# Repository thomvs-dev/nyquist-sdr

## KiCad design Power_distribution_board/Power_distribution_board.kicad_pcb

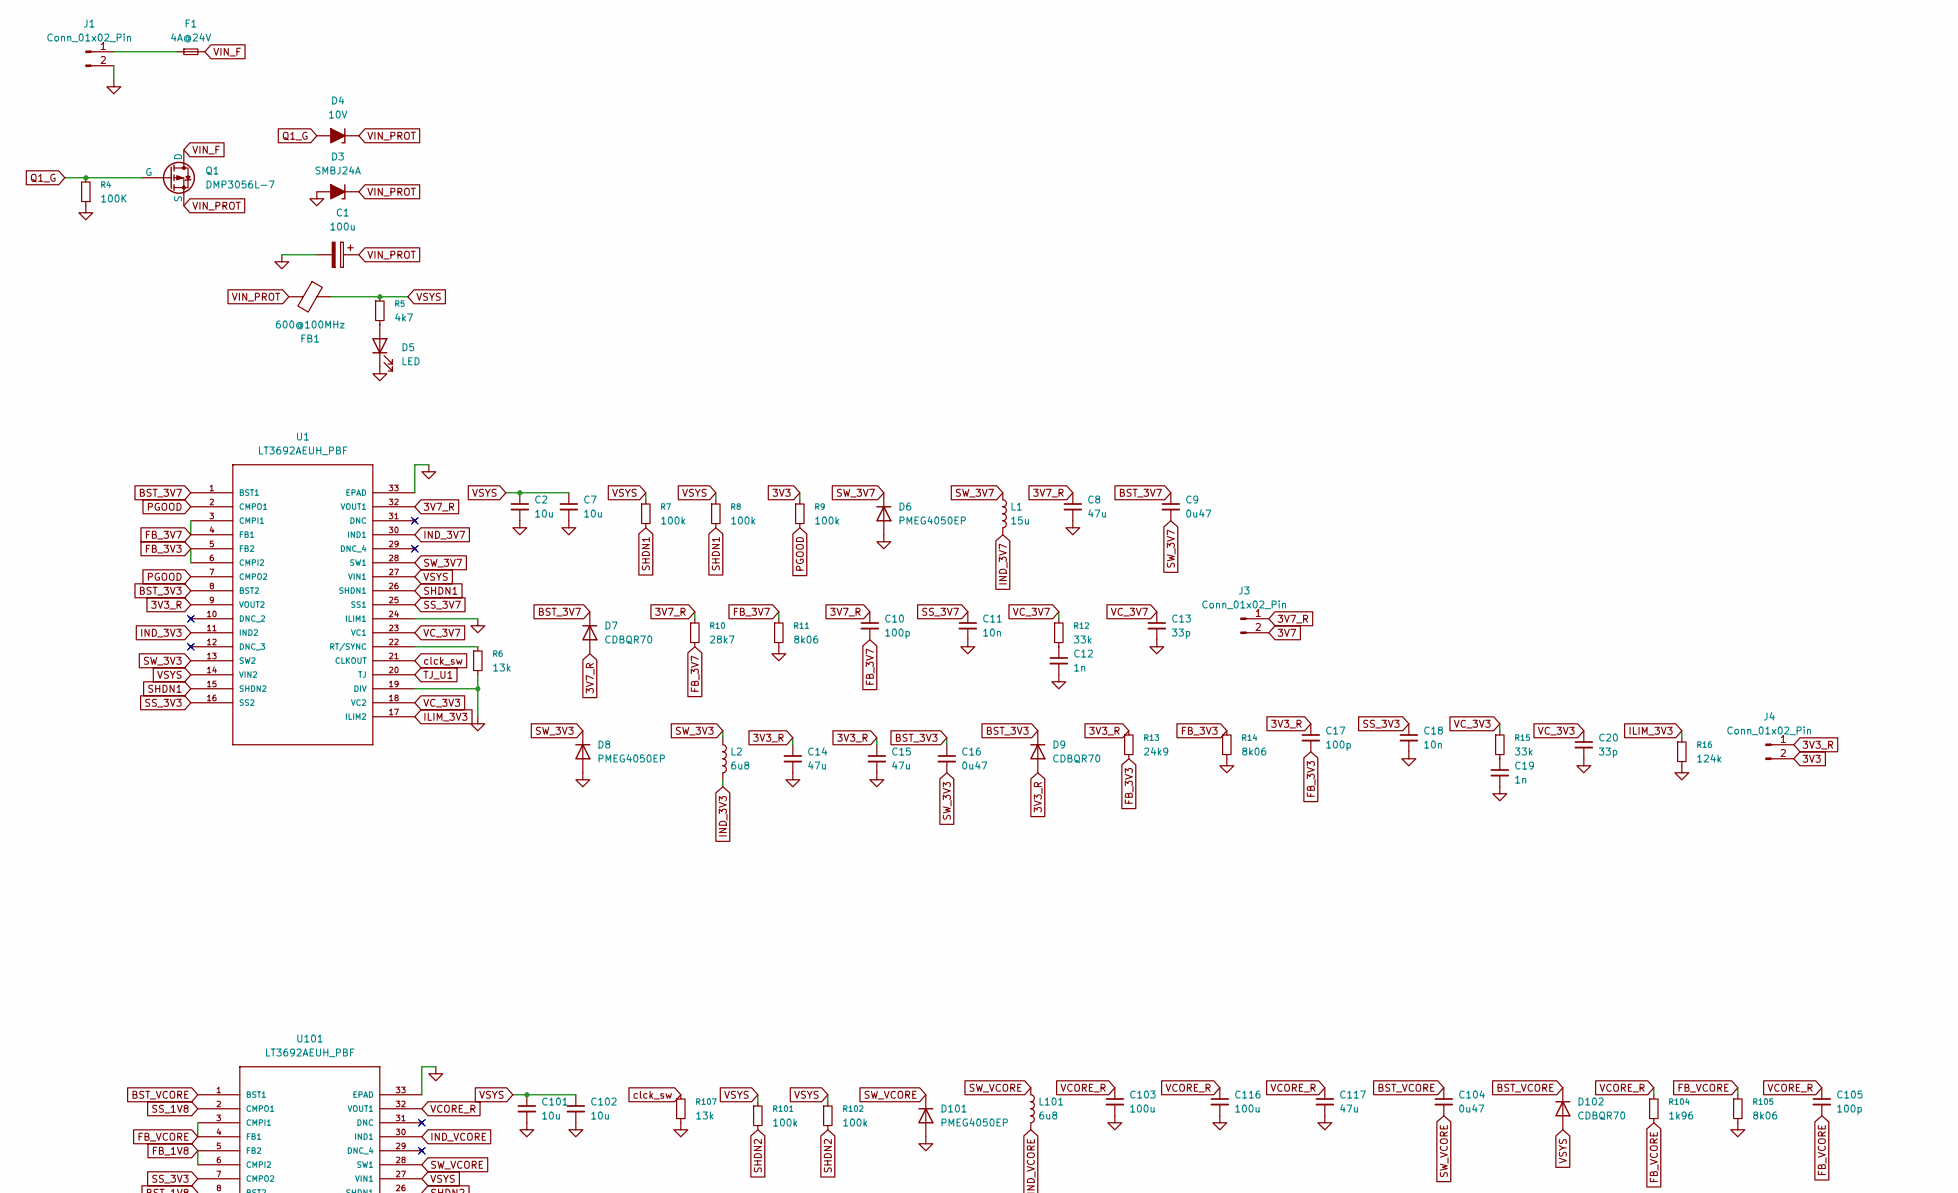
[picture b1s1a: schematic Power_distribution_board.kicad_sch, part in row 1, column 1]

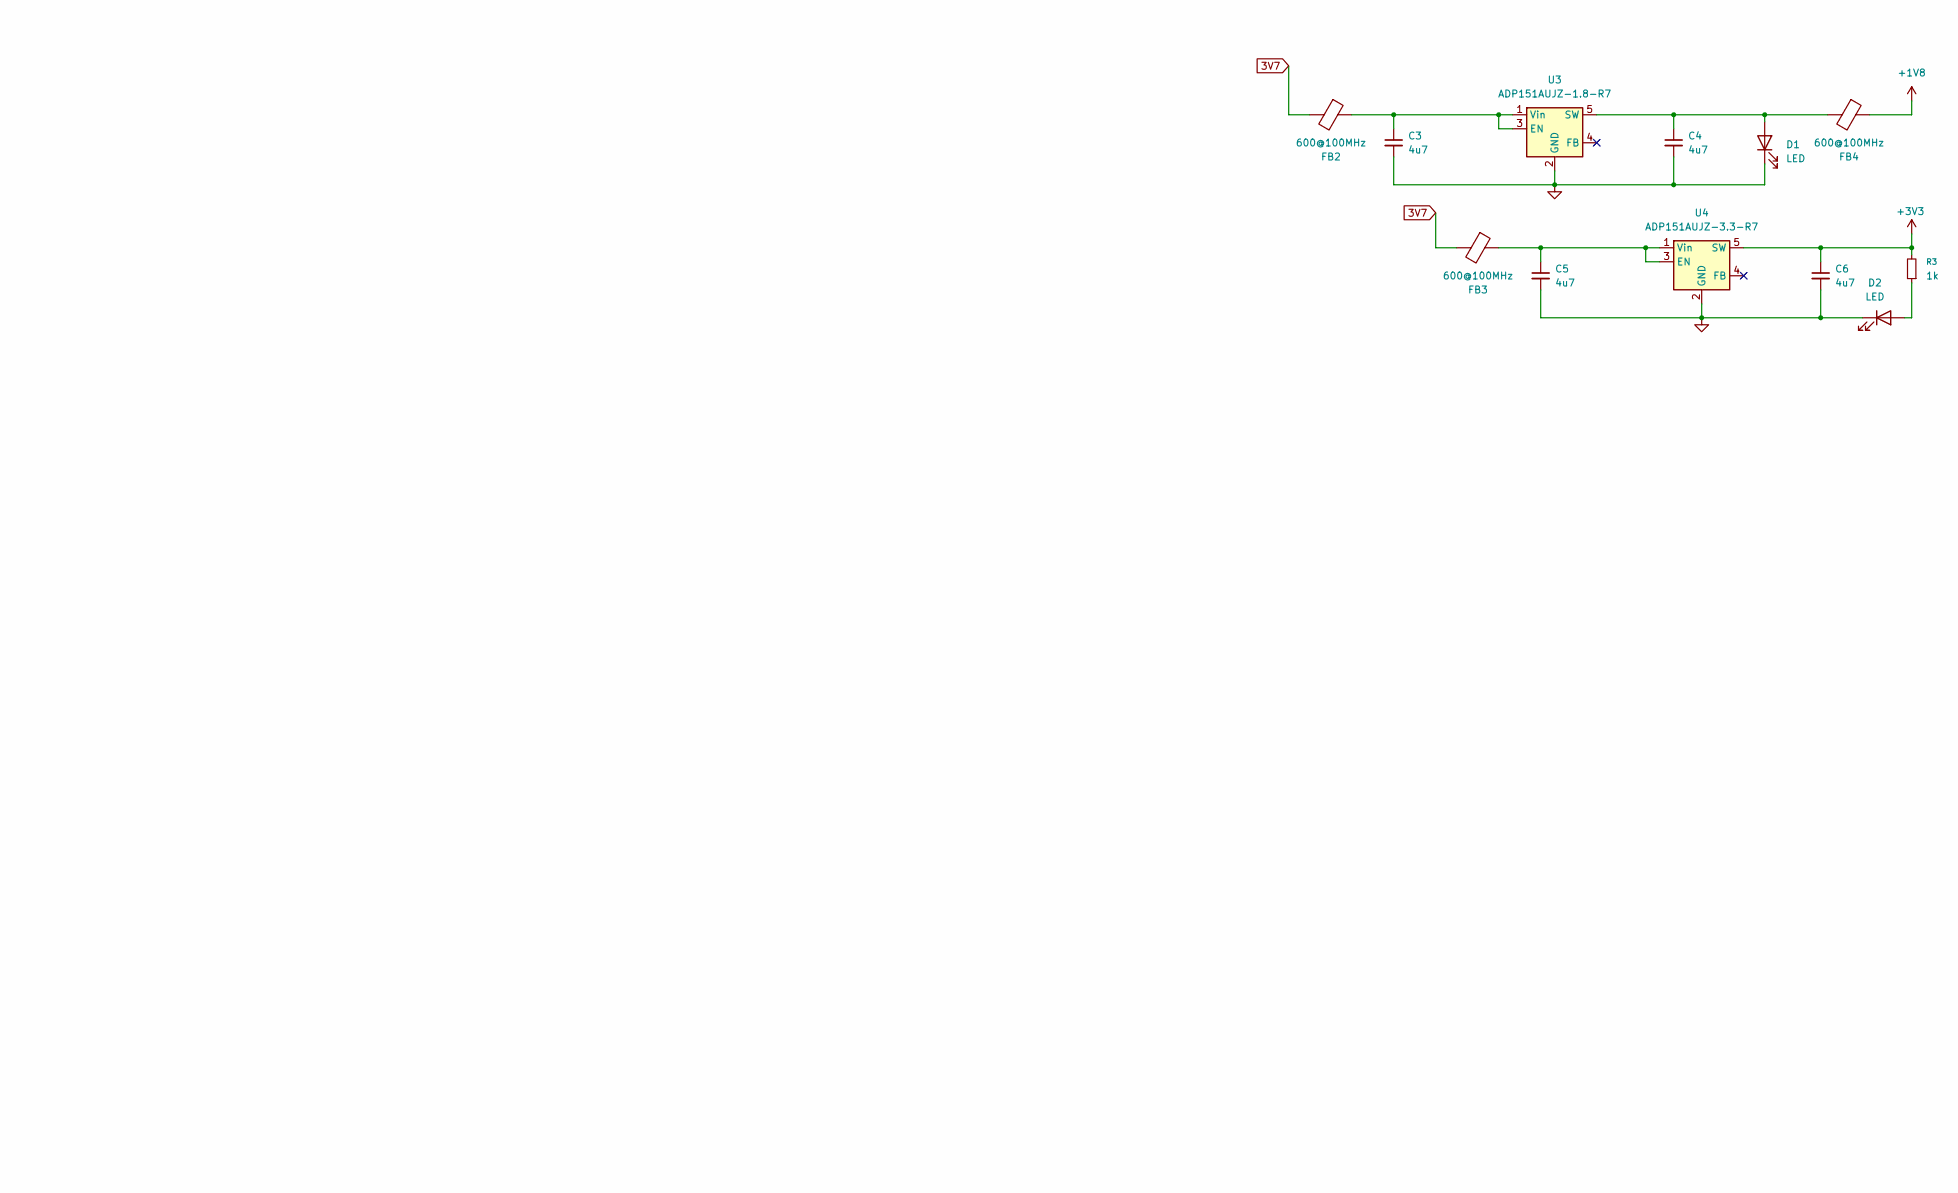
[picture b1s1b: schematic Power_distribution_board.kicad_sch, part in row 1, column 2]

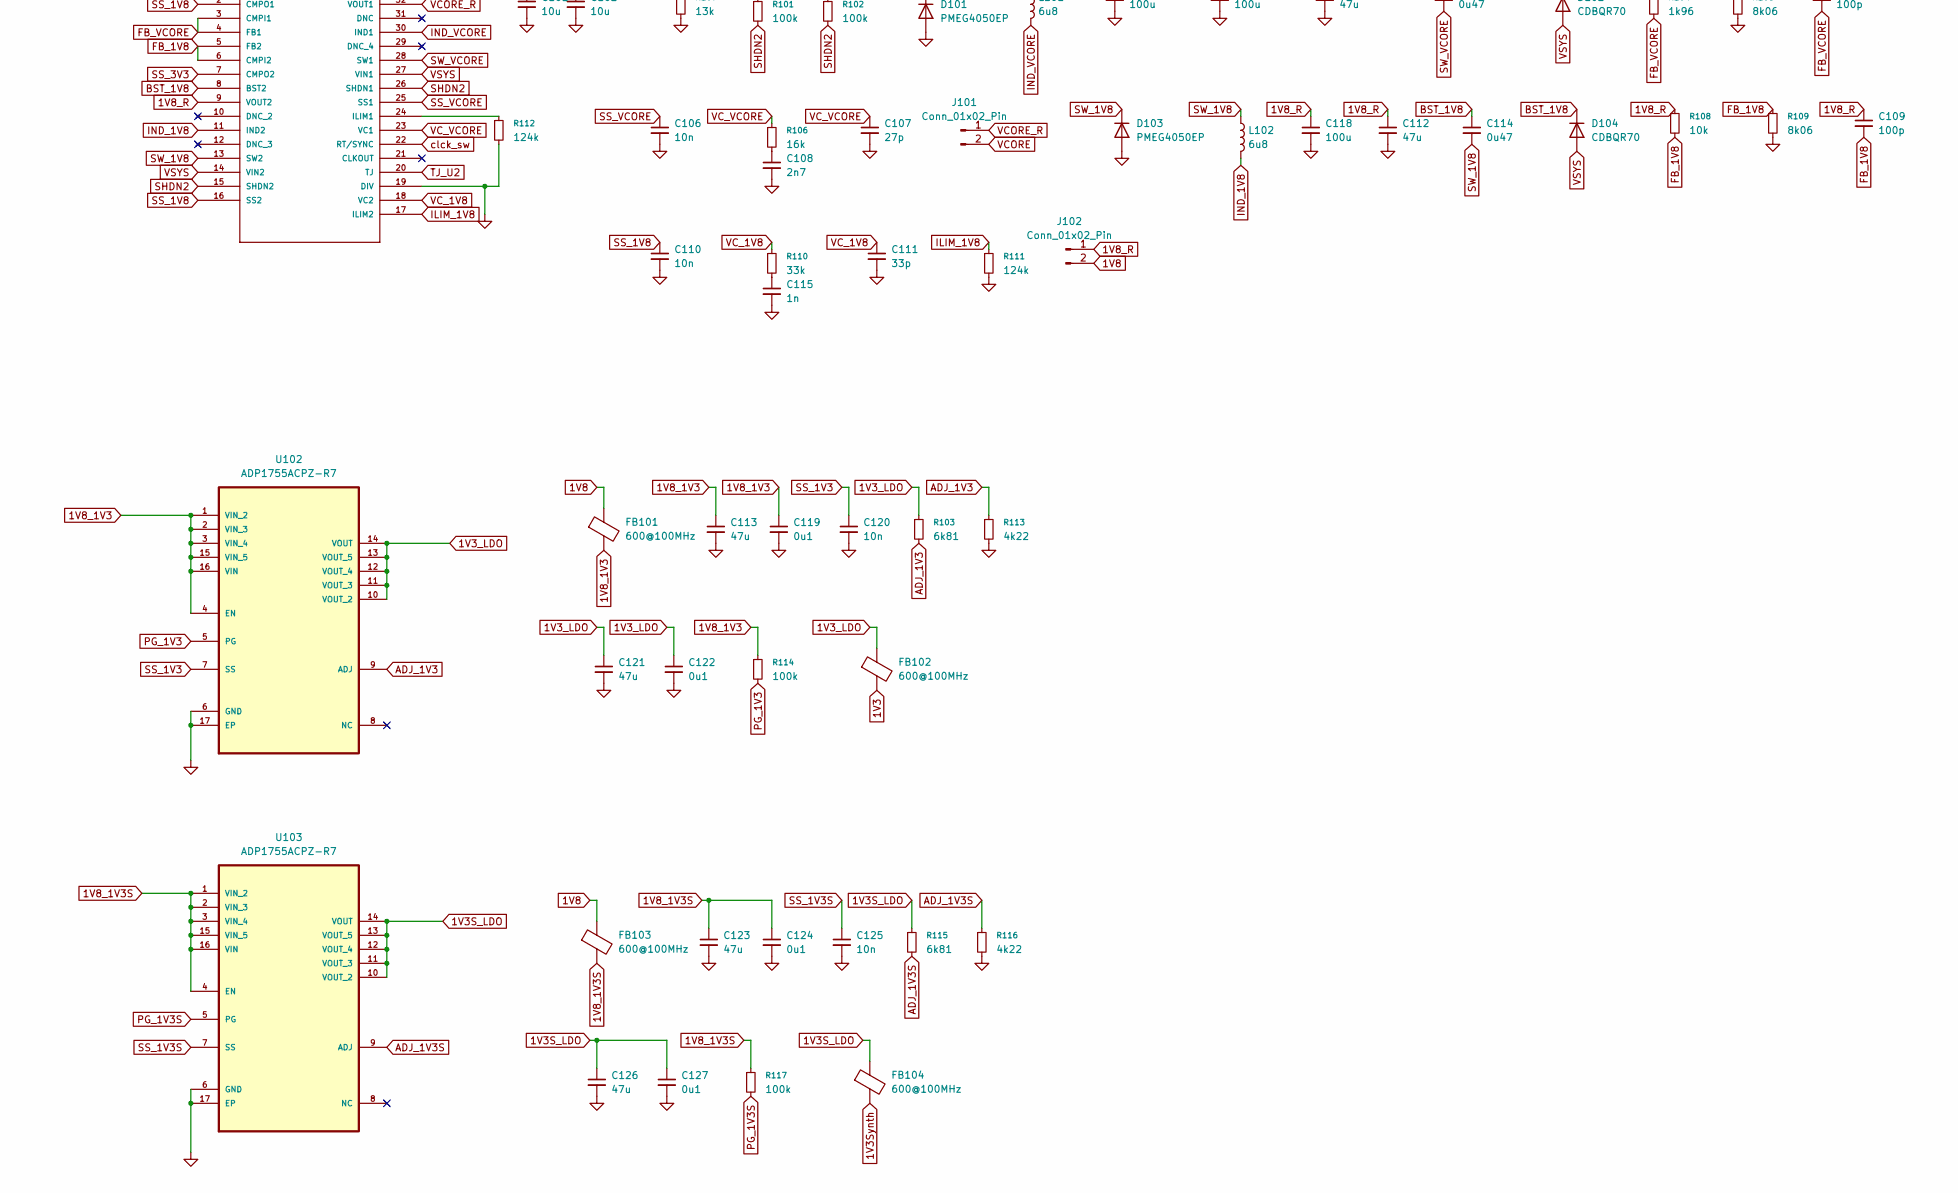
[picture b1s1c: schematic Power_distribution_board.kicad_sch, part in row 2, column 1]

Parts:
C1: 100u; CP_Elec_6.3x7.7
C2, C7, C101, C102: 10u; C_1206_3216Metric
C3, C4, C5, C6: 4u7; C_0402_1005Metric
C8, C14, C15, C112: 47u; C_0603_1608Metric
C9, C16, C104, C114: 0u47; C_0603_1608Metric
C10, C17, C105, C109: 100p; C_0201_0603Metric
C11, C18, C106, C110, C120, C125: 10n; C_0201_0603Metric
C12, C19, C115: 1n; C_0402_1005Metric
C13, C20, C111: 33p; C_0201_0603Metric
C103, C116, C118: 100u; C_1206_3216Metric
C107: 27p; C_0201_0603Metric
C108: 2n7; C_0402_1005Metric
C113, C117, C121, C123, C126: 47u; C_0402_1005Metric
C119, C122, C124, C127: 0u1; C_0402_1005Metric
D1, D2, D5: LED; LED_0603_1608Metric
D3: SMBJ24A; D_SMB
D4: 10V; D_SOD-123F; MPN BZT52C10
D6, D8, D101, D103: PMEG4050EP; D_SOD-128
D7, D9, D102, D104: CDBQR70; D_0402_1005Metric
F1: 4A@24V; Fuse_1206_3216Metric_Pad1.42x1.75mm_HandSolder; MPN SF-1206F400-2
FB1: 600@100MHz; L_1210_3225Metric; mpn FBMH3225HM601NT
FB2, FB3, FB4, FB101, FB102, FB103, FB104: 600@100MHz; L_1206_3216Metric; mpn MI1206K601R-10
J1: Conn_01x02_Pin; BarrelJack_CUI_PJ-063AH_Horizontal
J3, J4, J101, J102: Conn_01x02_Pin; PinHeader_1x02_P2.54mm_Vertical
L1: 15u; IND_XAL6060-153MEC
L2, L101, L102: 6u8; IND_XAL6060-153MEC
Q1: DMP3056L-7; SOT-23-3
R3: 1k; R_0402_1005Metric
R4: 100K; R_0402_1005Metric
R5: 4k7; R_0402_1005Metric
R6, R107: 13k; R_0402_1005Metric
R7, R8, R9, R101, R102, R114, R117: 100k; R_0402_1005Metric
R10: 28k7; R_0402_1005Metric
R11, R14, R105, R109: 8k06; R_0402_1005Metric
R12, R15, R110: 33k; R_0402_1005Metric
R13: 24k9; R_0402_1005Metric
R16, R111, R112: 124k; R_0402_1005Metric
R103, R115: 6k81; R_0402_1005Metric
R104: 1k96; R_0402_1005Metric
R106: 16k; R_0402_1005Metric
R108: 10k; R_0402_1005Metric
R113, R116: 4k22; R_0402_1005Metric
U1, U101: LT3692AEUH_PBF; QFN-32-1EP_5x5mm_P0.5mm_EP3.3x3.3mm_ThermalVias; MANUFACTURER_PART_NUMBER lt3692aeuh#pbf
U3: ADP151AUJZ-1.8-R7; TSOT-23-5
U4: ADP151AUJZ-3.3-R7; TSOT-23-5
U102, U103: ADP1755ACPZ-R7; Texas_RTY_WQFN-16-1EP_4x4mm_P0.65mm_EP2.1x2.1mm_ThermalVias; MPN ADP1755ACPZ-R7

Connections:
1V3: FB102.2
1V3S_LDO: C126.1, C127.1, FB104.1, R115.1, U103.10 (VOUT_2), U103.11 (VOUT_3), U103.12 (VOUT_4), U103.13 (VOUT_5), U103.14 (VOUT)
1V3Synth: FB104.2
1V3_LDO: C121.1, C122.1, FB102.1, R103.1, U102.10 (VOUT_2), U102.11 (VOUT_3), U102.12 (VOUT_4), U102.13 (VOUT_5), U102.14 (VOUT)
1V8: FB101.1, FB103.1, J102.2
1V8_1V3: C113.1, C119.1, FB101.2, R114.1, U102.1 (VIN_2), U102.2 (VIN_3), U102.3 (VIN_4), U102.4 (EN), U102.15 (VIN_5), U102.16 (VIN)
1V8_1V3S: C123.1, C124.1, FB103.2, R117.1, U103.1 (VIN_2), U103.2 (VIN_3), U103.3 (VIN_4), U103.4 (EN), U103.15 (VIN_5), U103.16 (VIN)
1V8_R: C109.1, C112.1, C118.1, J102.1, R108.1, U101.9 (VOUT2)
3V3: J4.2, R9.1
3V3_R: C14.1, C15.1, C17.1, D9.2 (A), J4.1, R13.1, U1.9 (VOUT2)
3V7: FB2.2, FB3.2, J3.2
3V7_R: C8.1, C10.1, D7.2 (A), J3.1, R10.1, U1.32 (VOUT1)
+1V8: FB4.1
+3V3: C6.1, R3.2, U4.5 (SW)
ADJ_1V3: R103.2, R113.1, U102.9 (ADJ)
ADJ_1V3S: R115.2, R116.1, U103.9 (ADJ)
BST_1V8: C114.1, D104.1 (K), U101.8 (BST2)
BST_3V3: C16.1, D9.1 (K), U1.8 (BST2)
BST_3V7: C9.1, D7.1 (K), U1.1 (BST1)
BST_VCORE: C104.1, D102.1 (K), U101.1 (BST1)
FB_1V8: C109.2, R108.2, R109.1, U101.5 (FB2), U101.6 (CMPI2)
FB_3V3: C17.2, R13.2, R14.1, U1.5 (FB2), U1.6 (CMPI2)
FB_3V7: C10.2, R10.2, R11.1, U1.3 (CMPI1), U1.4 (FB1)
FB_VCORE: C105.2, R104.2, R105.1, U101.3 (CMPI1), U101.4 (FB1)
GND: C1.2, C2.2, C3.2, C4.2, C5.2, C6.2, C7.2, C8.2, C11.2, C12.2, C13.2, C14.2, C15.2, C18.2, C19.2, C20.2, C101.2, C102.2, C103.2, C106.2, C107.2, C108.2, C110.2, C111.2, C112.2, C113.2, C115.2, C116.2, C117.2, C118.2, C119.2, C120.2, C121.2, C122.2, C123.2, C124.2, C125.2, C126.2, C127.2, D1.1 (K), D2.1 (K), D3.2 (A), D5.1 (K), D6.2 (A), D8.2 (A), D101.2 (A), D103.2 (A), J1.2, R4.1, R6.2, R11.2, R14.2, R16.2, R105.2, R107.2, R109.2, R111.2, R112.2, R113.2, R116.2, U1.19 (DIV), U1.24 (ILIM1), U1.33 (EPAD), U3.2 (GND), U4.2 (GND), U101.19 (DIV), U101.33 (EPAD), U102.6 (GND), U102.17 (EP), U103.6 (GND), U103.17 (EP)
ILIM_1V8: R111.1, U101.17 (ILIM2)
ILIM_3V3: R16.1, U1.17 (ILIM2)
IND_1V8: L102.2, U101.11 (IND2)
IND_3V3: L2.2, U1.11 (IND2)
IND_3V7: L1.2, U1.30 (IND1)
IND_VCORE: L101.2, U101.30 (IND1)
unnamed: C12.1, R12.2
unnamed: C19.1, R15.2
unnamed: C108.1, R106.2
unnamed: C115.1, R110.2
unnamed: C4.1, D1.2 (A), FB4.2, U3.5 (SW)
unnamed: D2.2 (A), R3.1
unnamed: D5.2 (A), R5.2
unnamed: F1.1, J1.1
unnamed: R6.1, U1.22 (RT/SYNC)
unnamed: C3.1, FB2.1, U3.1 (Vin), U3.3 (EN)
unnamed: C5.1, FB3.1, U4.1 (Vin), U4.3 (EN)
unnamed: R112.1, U101.24 (ILIM1)
PGOOD: R9.2, U1.2 (CMPO1), U1.7 (CMPO2)
PG_1V3: R114.2, U102.5 (PG)
PG_1V3S: R117.2, U103.5 (PG)
Q1_G: D4.2 (A), Q1.2 (G), R4.2
SHDN1: R7.2, R8.2, U1.15 (SHDN2), U1.26 (SHDN1)
SHDN2: R101.2, R102.2, U101.15 (SHDN2), U101.26 (SHDN1)
SS_1V3: C120.1, U102.7 (SS)
SS_1V3S: C125.1, U103.7 (SS)
SS_1V8: C110.1, U101.2 (CMPO1), U101.16 (SS2)
SS_3V3: C18.1, U1.16 (SS2), U101.7 (CMPO2)
SS_3V7: C11.1, U1.25 (SS1)
SS_VCORE: C106.1, U101.25 (SS1)
SW_1V8: C114.2, D103.1 (K), L102.1, U101.13 (SW2)
SW_3V3: C16.2, D8.1 (K), L2.1, U1.13 (SW2)
SW_3V7: C9.2, D6.1 (K), L1.1, U1.28 (SW1)
SW_VCORE: C104.2, D101.1 (K), L101.1, U101.28 (SW1)
TJ_U1: U1.20 (TJ)
TJ_U2: U101.20 (TJ)
VCORE: J101.2
VCORE_R: C103.1, C105.1, C116.1, C117.1, J101.1, R104.1, U101.32 (VOUT1)
VC_1V8: C111.1, R110.1, U101.18 (VC2)
VC_3V3: C20.1, R15.1, U1.18 (VC2)
VC_3V7: C13.1, R12.1, U1.23 (VC1)
VC_VCORE: C107.1, R106.1, U101.23 (VC1)
VIN_F: F1.2, Q1.1 (D)
VIN_PROT: C1.1, D3.1 (K), D4.1 (K), FB1.2, Q1.3 (S)
VSYS: C2.1, C7.1, C101.1, C102.1, D102.2 (A), D104.2 (A), FB1.1, R5.1, R7.1, R8.1, R101.1, R102.1, U1.14 (VIN2), U1.27 (VIN1), U101.14 (VIN2), U101.27 (VIN1)
clck_sw: R107.1, U1.21 (CLKOUT), U101.22 (RT/SYNC)

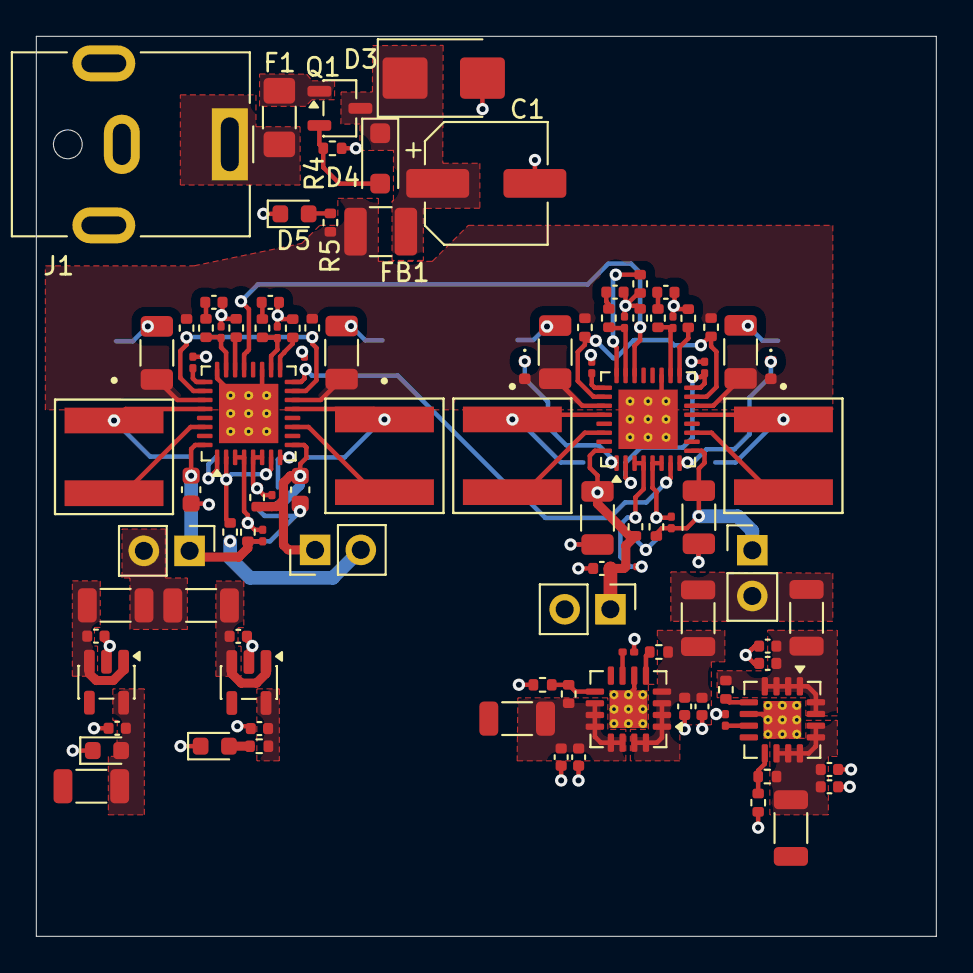
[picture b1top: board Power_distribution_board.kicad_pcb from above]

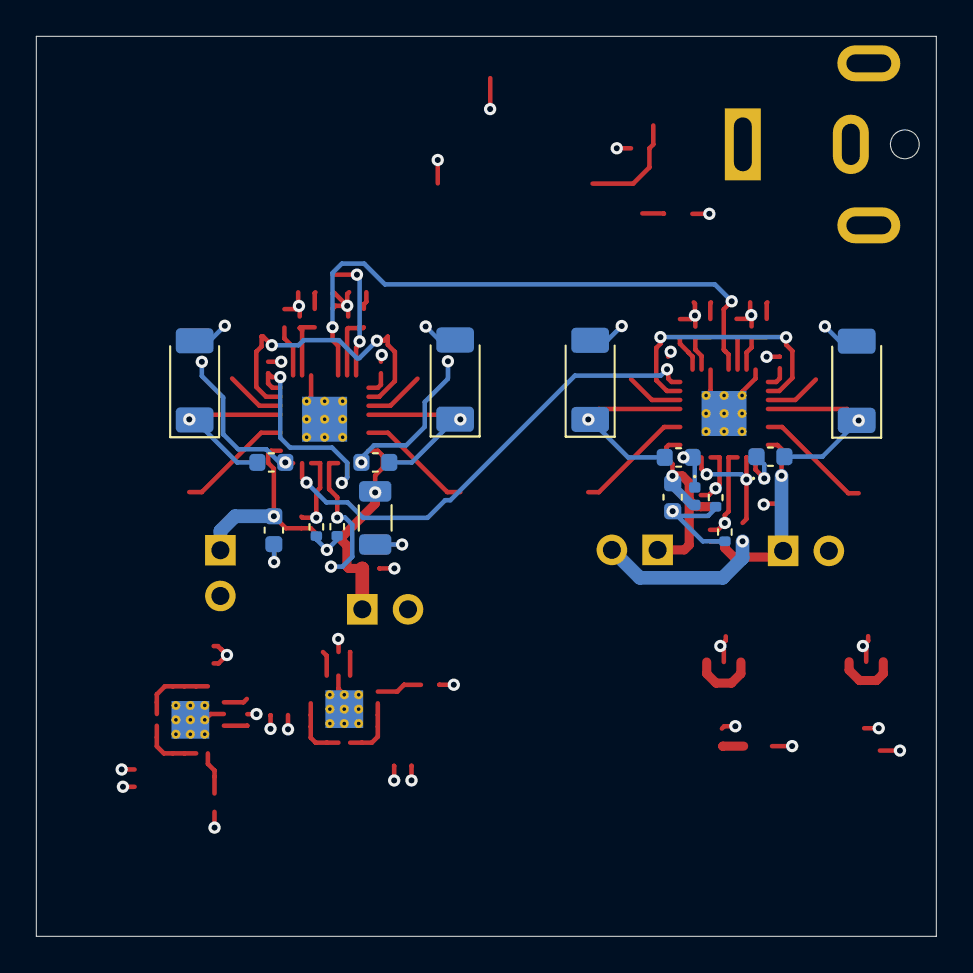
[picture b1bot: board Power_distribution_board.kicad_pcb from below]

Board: 4 copper layers, 50.0 x 50.0 mm, 116 parts (17 on the bottom side), 65 nets.

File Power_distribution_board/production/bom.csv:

Designator,Footprint,Quantity,Value,LCSC Part #
C1,CP_Elec_6.3x7.7,1,100u,
"C10, C17",0201,2,100p,
"C11, C18",0201,2,10n,
"C12, C19",0402,2,1n,
"C13, C20",0201,2,33p,
"C14, C15, C8",0402,3,47u,
"C16, C9",0603,2,0u47,
"C2, C7",1206,2,10u,
"C3, C4, C5, C6",0402,4,4u7,
"D1, D2, D5",0402,3,LED,
D3,D_SMB,1,SMBJ24A,
D4,D_SOD-123F,1,10V,BZT52C10
"D6, D8",D_SOD-128,2,PMEG4050EP,
"D7, D9",0402,2,CDBQR70,
F1,1206,1,4A@24V,SF-1206F400-2
FB1,1210,1,600@100MHz,FBMH3225HM601NT
"FB2, FB3, FB4",1206,3,600@100MHz,MI1206K601R-10
J1,BarrelJack_CUI_PJ-063AH_Horizontal,1,Conn_01x02_Pin,
"J3, J4",PinHeader_1x02_P2.54mm_Vertical,2,Conn_01x02_Pin,
L1,IND_XAL6060-153MEC,1,15u,
L2,IND_XAL6060-153MEC,1,6u8,
Q1,SOT-23-3,1,PMOS,
R10,0402,1,28k7,
"R11, R14",0402,2,8k06,
"R12, R15",0402,2,33k,
R13,0402,1,24k9,
R16,0402,1,124k,
R3,0402,1,1k,
"R4, R7, R8, R9",0402,4,100K,
R5,0402,1,4k7,
R6,0402,1,13k,
U1,QFN-32-1EP_5x5mm_P0.5mm_EP3.3x3.3mm_ThermalVias,1,LT3692AEUH_PBF,
U3,TSOT-23-5,1,ADP151AUJZ-1.8-R7,
U4,TSOT-23-5,1,ADP151AUJZ-3.3-R7,
